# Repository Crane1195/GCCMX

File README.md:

# GCCMX
A digital controller PCB/chassis design.

The PCB is originally designed to allow mounting a Model S and a Brook board, but you can also just solder wires to the through holes. The pin holes are labeled on the silk screen of the board.

## License
This project is licenced under the GNU GPL Version 3. [See the included LICENSE file for details](LICENSE).

## Support my work
I set up a donation link for people who appreciate my work and wish to donate. Donations are greatly appreciated, but are far from necessary:

https://www.paypal.com/donate/?hosted_button_id=NFDEML5FKR8N8

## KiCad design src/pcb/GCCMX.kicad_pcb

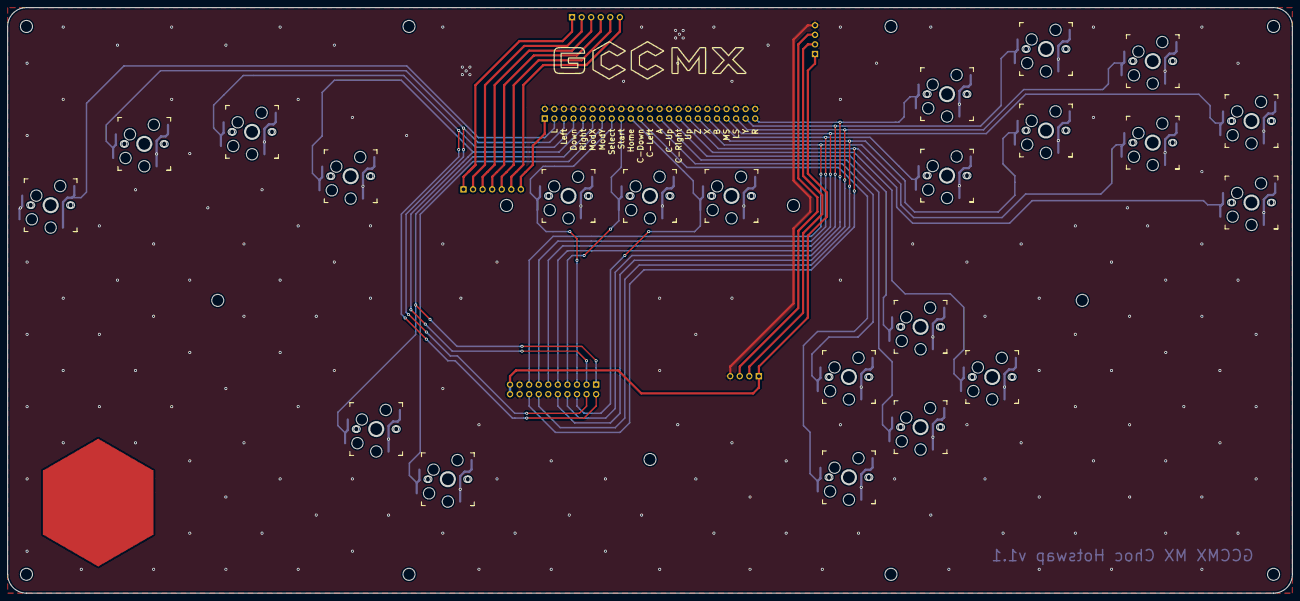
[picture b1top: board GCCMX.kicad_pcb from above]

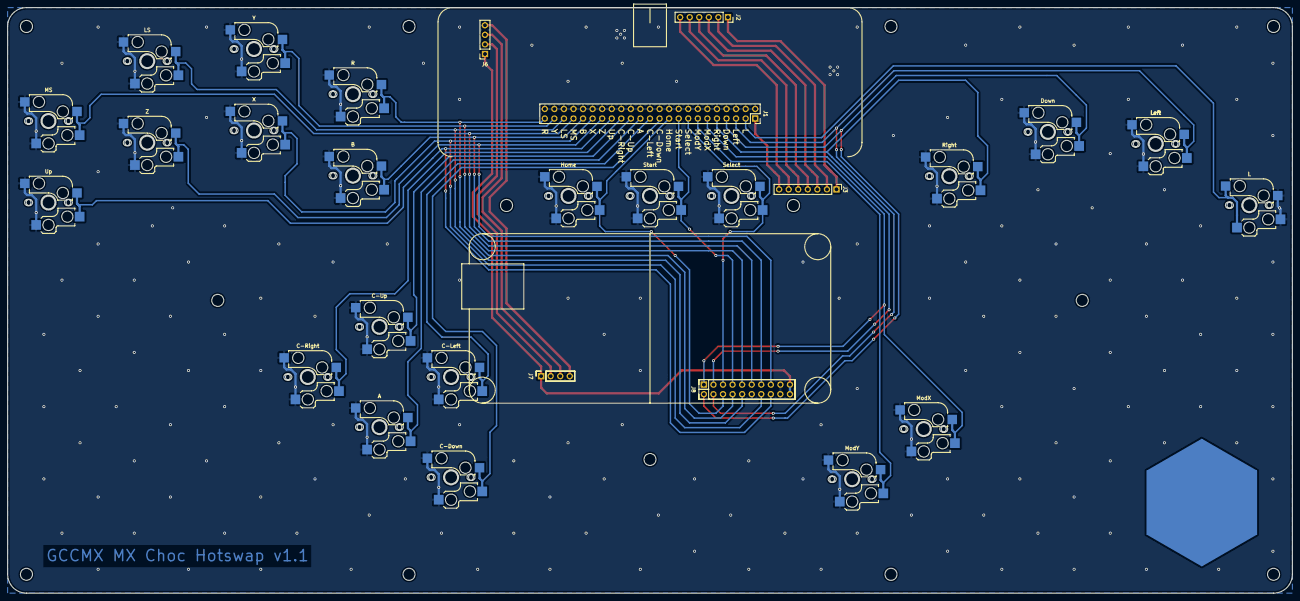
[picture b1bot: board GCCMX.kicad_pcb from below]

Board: 2 copper layers, 341.2 x 155.5 mm, 28 parts (6 on the bottom side), 33 nets.

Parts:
A: SW_SPST; Kailh_socket_MX+PG1350
B: SW_SPST; Kailh_socket_MX+PG1350
C-Down: SW_SPST; Kailh_socket_MX+PG1350
C-Left: SW_SPST; Kailh_socket_MX+PG1350
C-Right: SW_SPST; Kailh_socket_MX+PG1350
C-Up: SW_SPST; Kailh_socket_MX+PG1350
Down: SW_SPST; Kailh_socket_MX+PG1350
Home: SW_SPST; Kailh_socket_MX+PG1350
J1: Inputs Female; PinSocket_2x23_P2.54mm_Vertical
J2: Debug In; PinSocket_1x06_P2.54mm_Vertical
J3: Debug Out; PinHeader_1x07_P2.54mm_Vertical
J6: USB-IN; PinSocket_1x04_P2.54mm_Vertical
J7: USB-OUT; PinSocket_1x04_P2.54mm_Vertical
J8: Brook Out; PinSocket_2x10_P2.54mm_Vertical
L: SW_SPST; Kailh_socket_MX+PG1350
LS: SW_SPST; Kailh_socket_MX+PG1350
Left: SW_SPST; Kailh_socket_MX+PG1350
MS: SW_SPST; Kailh_socket_MX+PG1350
ModX: SW_SPST; Kailh_socket_MX+PG1350
ModY: SW_SPST; Kailh_socket_MX+PG1350
R: SW_SPST; Kailh_socket_MX+PG1350
Right: SW_SPST; Kailh_socket_MX+PG1350
Select: SW_SPST; Kailh_socket_MX+PG1350
Start: SW_SPST; Kailh_socket_MX+PG1350
Up: SW_SPST; Kailh_socket_MX+PG1350
X: SW_SPST; Kailh_socket_MX+PG1350
Y: SW_SPST; Kailh_socket_MX+PG1350
Z: SW_SPST; Kailh_socket_MX+PG1350

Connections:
/A: A.2, J1.25
/B: B.2, J1.37, J8.13
/C-D: C-Down.2, J1.21
/C-L: C-Left.2, J1.23
/C-R: C-Right.2, J1.29
/C-U: C-Up.2, J1.27
/Down: Down.2, J1.7, J8.2
/Home: Home.2, J1.19, J8.6
/L: J1.3, L.1
/LS: J1.41, J8.10, LS.2
/Left: J1.5, J8.4, Left.2
/MS: J1.39, J8.11, MS.2
/ModX: J1.11, J8.1, ModX.2
/ModY: J1.13, ModY.2
/R: J1.45, J8.8, R.2
/Right: J1.9, J8.3, Right.2
/Select: J1.15, J8.5, Select.2
/Start: J1.17, J8.7, Start.2
/TXLED: J1.1, J3.7
/Up: J1.31, J8.16, Up.2
/X: J1.35, J8.14, X.2
/Y: J1.43, J8.9, Y.2
/Z: J1.33, J8.15, Z.2
GND: A.1, B.1, C-Down.1, C-Left.1, C-Right.1, C-Up.1, Down.1, Home.1, J1.2, J1.4, J1.6, J1.8, J1.10, J1.12, J1.14, J1.16, J1.18, J1.20, J1.22, J1.24, J1.26, J1.28, J1.30, J1.32, J1.34, J1.36, J1.38, J1.40, J1.42, J1.44, J1.46, J6.4, J7.4, J8.12, J8.17, J8.18, L.2, LS.1, Left.1, MS.1, ModX.1, ModY.1, R.1, Right.1, Select.1, Start.1, Up.1, X.1, Y.1, Z.1
unnamed: J2.1, J3.1
unnamed: J2.2, J3.2
unnamed: J2.3, J3.3
unnamed: J2.4, J3.4
unnamed: J2.5, J3.5
unnamed: J2.6, J3.6
unnamed: J6.2, J7.2
unnamed: J6.3, J7.3
VBUS: J6.1, J7.1, J8.19, J8.20

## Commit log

2022-03-05 Add PCB, Chassis, Readme, IMG
